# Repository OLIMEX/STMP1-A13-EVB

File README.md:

# STMP1-A13-EVB
Evaluation board for STMP15x-SOM and A13-SOM System on modules

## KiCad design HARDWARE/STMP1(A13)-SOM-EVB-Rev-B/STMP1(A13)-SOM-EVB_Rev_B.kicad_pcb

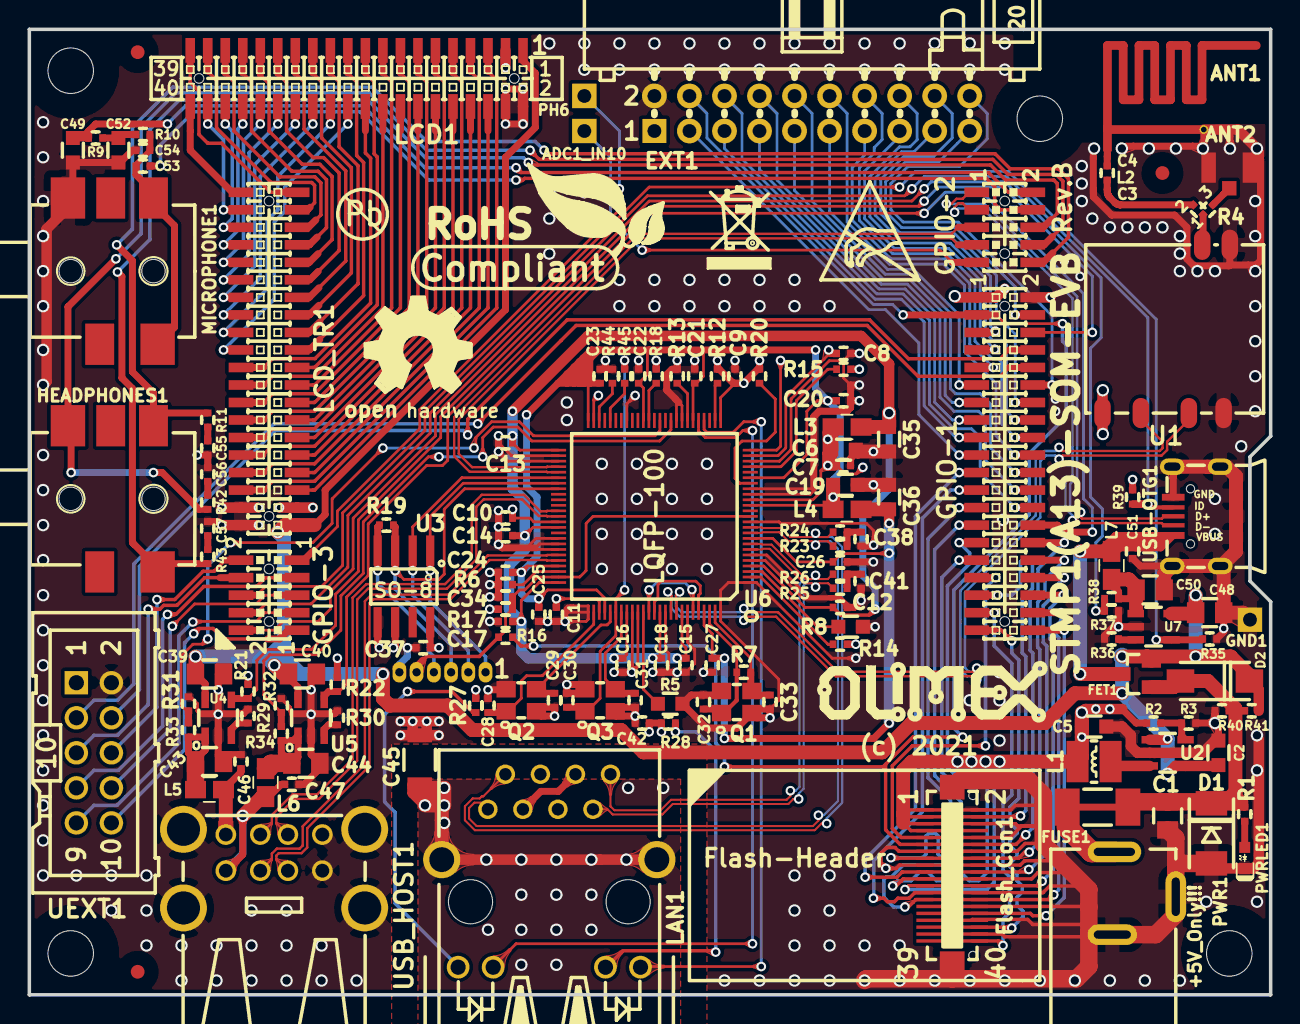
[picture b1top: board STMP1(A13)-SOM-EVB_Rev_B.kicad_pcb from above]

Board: 4 copper layers, 90.0 x 70.0 mm, 157 parts (1 on the bottom side), 164 nets.

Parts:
ADC1_IN10: TESTPAD; TEST_PAD40x70_SQUARE
ANT1: WIFI_ANT; WIFI_ANT_ESP8266_ANT(1)_GND(2)_NO_MASK
ANT2: U.FL-R-SMT-1
C1, C39, C40, C43, C44, C48, C50: 47uF/6.3V/20%/X5R/C0805; C_0805_5MIL_DWS
C2, C5, C6, C19, C35, C36, C49, C52: 10uF/6.3V/20%/X5R/C0603; C_0603_5MIL_DWS
C3, C4: NA/C0402; C_0402_5MIL_DWS
C7, C8, C9, C10, C11, C12, C13, C14, C15, C16, C17, C18, C20, C21, C22, C23, C24, C25, C26, C27, C34, C37, C38, C41, C42, C46, C47, C51, C53, C55, C56, C57: 100nF/10V/10%/X5R/C0402; C_0402_5MIL_DWS
C28, C29, C32, C33: 33pF/50V/5%/COG/C0402; C_0402_5MIL_DWS
C30, C31: NA(33pF/50V/5%/COG/C0402); C_0402_5MIL_DWS
C45: 1nF/2000V/10%/X7R/C1206; C_1206_5MIL_DWS_ISO
C54: 3.3nF/50V/10%/X5R/C0402; C_0402_5MIL_DWS
D1: SMBJ6.0A; DO214AA_1(K)-2(A)
D2: 1N5822/SMA; SMA-KA
EXT1: BH20R
FET1: WPM2015-3/TR; SOT23
FID1, FID2, FID3: Fiducial; Fiducial1x3
FUSE1: NA(5025); FUSE-5025
Flash_Con1: Flash_Con[DF12(3.0)-40DS-0.5V(86)]
GND1: TESTPAD; TEST_PAD40x70_SQUARE
GPIO-1: PA-V16X-2X20-LF; GPH127SMT-02X20(PA-V16X-2X20-LF)
GPIO-2, GPIO-3: PA-V16X-2X5-LF; GPH127SMT-02X05(PA-V16X-2X5-LF)
HEADPHONES1: SCJ325P00XG0B02G
L1: 2.2uH/1.5A/DCR=72mR/20%/3.00x3.00x1.50mm/CD32(NR3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; CD32
L2: 0R/R0402; L_0402_5MIL_DWS
L3, L4, L5, L6, L7: FB0805/600R/2A; L_0805_5MIL_DWS
LAN1: RJLD-060TC1(LPJ4013EDNL); RJLBC-060TC1
LCD1: PA-V16X-2X20-LF; GPH127SMT-02X20(PA-V16X-2X20-LF)
LCD_TR1: PA-V16X-2X20-LF; GPH127SMT-02X20(PA-V16X-2X20-LF)
Logo_OSHW: LOGO_OPENHARDWARE_8x8
Logo_Olimex: OLIMEX_LOGO_TB
MH1, MH2, MH3, MH4: NPTH; Mounting_Hole_Drill-3.3mm_Clerance-7mm
MICROPHONE1: SCJ325P00XG0B02G
PGM1: NA(WU06S); WU06S
PH6: TESTPAD; TEST_PAD40x70_SQUARE
PWR1: PWRJ-2mm(YDJ-1134)
PWRLED1: LED/Red/0603; LED_0603_KA
Q1: Q25MHZ/20pF/20ppm/4P/3.2x2.5mm; TSX-3.2x2.5mm_GND(3)
Q2: Q12MHZ/20pF/10ppm/4P/3.2x2.5mm; TSX-3.2x2.5mm_GND(3)
Q3: NA(Q12MHZ/20pF/10ppm/4P/3.2x2.5mm); TSX-3.2x2.5mm_GND(3)
R1, R9, R10, R44: 2.2k/R0402; R_0402_5MIL_DWS
R2: 4.99k/1%/R0402; R_0402_5MIL_DWS
R3: 1.1k/1%/R0402; R_0402_5MIL_DWS
R4: 0R/R0402(Default_1-2_Populated); ANT_SWITCH-R0402
R5, R8: 12.1k/1%/R0603; R_0603_5MIL_DWS
R6: 680R/1%/R0402; R_0402_5MIL_DWS
R7: 1M/R0402; R_0402_5MIL_DWS
R11, R19, R42, R43, R45: 22R/R0402; R_0402_5MIL_DWS
R12, R13, R14, R17, R21, R22, R31, R32, R35, R37, R39, R40: 10k/R0402; R_0402_5MIL_DWS
R15, R18, R33, R34, R38: 4.7k/R0402; R_0402_5MIL_DWS
R16, R41: NA/R0402; R_0402_5MIL_DWS
R20: NA(10k/R0402); R_0402_5MIL_DWS
R23, R24, R25, R26: 49.9R/1%/R0402; R_0402_5MIL_DWS
R27, R28: 330R/R0402; R_0402_5MIL_DWS
R29, R30, R36: 13k/1%/R0402; R_0402_5MIL_DWS
Sign_Antistatic: Val**; LOGO_ANTISTATIC_1
Sign_PB-Free: LOGO_PBFREE
Sign_RecycleBin: LOGO_RECYCLEBIN_1
Sign_RoHS: Val**; LOGO_ROHS_1
U1: MOD-RL-UM12BS-8188ETV
U2: SY8089AAAC(SOT23-5); SOT-23-5
U3: 93LC66C-I/SN(SO-8); SO-8
U4, U5, U7: SY6280AAC(SOT23-5); SOT-23-5
U6: AX88760LF(LQFP-100); LQFP-100_Pitch-0.4mm_Dimensions-12.00x12.00x1.60mm
UEXT1: BH10S
USB-OTG1: MICRO_USB\MISB-SWMM-5B_LF; USB-MICRO_MISB-SWMM-5B_LF
USB_HOST1: USBB1-FRWH-4A(USB-Ax2); USB_TWO_LEVEL

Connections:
(IO2): Flash_Con1.23, GPIO-1.29
(IO3): Flash_Con1.21, GPIO-1.31
+1.8VA: C26.1, C27.1, C36.1, L4.2, U6.9, U6.97
+3.3VA: C12.1, C13.1, C14.1, C15.1, C16.1, C17.1, C18.1, C35.1, L3.2, U6.4, U6.51, U6.65, U6.75, U6.83, U6.89, U6.93
+3V3: C5.1, C6.2, C7.1, C8.1, C9.1, C10.1, C11.1, C37.2, C42.1, EXT1.1, Flash_Con1.1, Flash_Con1.3, Flash_Con1.5, Flash_Con1.7, GPIO-1.1, L1.2, L3.1, LAN1.3, LAN1.6, LCD1.3, LCD_TR1.3, R2.2, R12.2, R14.2, R15.2, R17.2, R18.2, R20.2, R21.1, R22.1, R27.1, R28.1, R39.2, U1.1, U3.6, U3.8, U6.16, U6.24, U6.26, U6.64, U6.78, UEXT1.1
+5V_EXT: C2.1, C39.1, C40.1, C48.1, D2.1, FET1.2, LCD1.1, LCD_TR1.1, R41.1, U2.1, U2.4, U4.5, U5.5, U7.5
+5V_USBOTG: C51.1, FET1.3, L7.2, USB-OTG1.1
/12MCK: C30.1, Q3.1, R45.2, U6.81
/+5V_USB1: C46.2, L5.2, USB_HOST1.1.1
/+5V_USB2: C47.2, L6.2, USB_HOST1.2.1
/D1+: U6.63, USB_HOST1.1.3
/D1-: U6.62, USB_HOST1.1.2
/D2+: U6.71, USB_HOST1.2.3
/D2-: U6.70, USB_HOST1.2.2
/D3+: U1.3, U6.92
/D3-: U1.2, U6.91
/ETHER_LK: LAN1.KY1, U6.30
/ETHER_SPEED: LAN1.KG1, U6.29
/ETH_SH: C45.1, LAN1.GND1, LAN1.GND2
/I2C2_SCL: EXT1.17, GPIO-1.5
/I2C2_SDA: EXT1.15, GPIO-1.7
/I2C5_SCL: LCD1.39, LCD_TR1.39
/I2C5_SDA: LCD1.40, LCD_TR1.40
/I2C6_SCL: EXT1.5, GPIO-1.17
/I2C6_SDA: EXT1.3, GPIO-1.19
/LCD_B0: LCD1.21, LCD_TR1.21
/LCD_B1: LCD1.22, LCD_TR1.22
/LCD_B2: LCD1.23, LCD_TR1.23
/LCD_B3: LCD1.24, LCD_TR1.24
/LCD_B4: LCD1.25, LCD_TR1.25
/LCD_B5: LCD1.26, LCD_TR1.26
/LCD_B6: LCD1.27, LCD_TR1.27
/LCD_B7: LCD1.28, LCD_TR1.28
/LCD_CLK: LCD1.31, LCD_TR1.31
/LCD_DE: LCD1.32, LCD_TR1.32
/LCD_G0: LCD1.13, LCD_TR1.13
/LCD_G1: LCD1.14, LCD_TR1.14
/LCD_G2: LCD1.15, LCD_TR1.15
/LCD_G3: LCD1.16, LCD_TR1.16
/LCD_G4: LCD1.17, LCD_TR1.17
/LCD_G5: LCD1.18, LCD_TR1.18
/LCD_G6: LCD1.19, LCD_TR1.19
/LCD_G7: LCD1.20, LCD_TR1.20
/LCD_HSYNC: LCD1.29, LCD_TR1.29
/LCD_INT: LCD1.37, LCD_TR1.37
/LCD_LR: LCD1.33, LCD_TR1.33
/LCD_PWM: LCD1.36, LCD_TR1.36
/LCD_PWRE: LCD1.35, LCD_TR1.35
/LCD_R0: LCD1.5, LCD_TR1.5
/LCD_R1: LCD1.6, LCD_TR1.6
/LCD_R2: LCD1.7, LCD_TR1.7
/LCD_R3: LCD1.8, LCD_TR1.8
/LCD_R4: LCD1.9, LCD_TR1.9
/LCD_R5: LCD1.10, LCD_TR1.10
/LCD_R6: LCD1.11, LCD_TR1.11
/LCD_R7: LCD1.12, LCD_TR1.12
/LCD_RST: LCD1.38, LCD_TR1.38
/LCD_UD: LCD1.34, LCD_TR1.34
/LCD_VSYNC: LCD1.30, LCD_TR1.30
/NRST: EXT1.4, Flash_Con1.11, GPIO-1.3, R16.2
/OVCUR1#: R31.2, R33.1, U6.37
/OVCUR2#: R32.2, R34.1, U6.35
/PA1: EXT1.19, GPIO-1.4
/PG8: EXT1.7, GPIO-1.15
/RST_PGM: C34.2, PGM1.5, R16.1, R17.1, U6.13, U6.74
/RXIN: LAN1.8, R26.2, U6.8
/RXIP: LAN1.7, R25.2, U6.7
/SDMMC3_CK: EXT1.16, GPIO-1.16
/SDMMC3_CMD: EXT1.14, GPIO-1.18
/SDMMC3_D0: EXT1.6, GPIO-1.26
/SDMMC3_D1: EXT1.8, GPIO-1.24
/SDMMC3_D2: EXT1.10, GPIO-1.22
/SDMMC3_D3: EXT1.12, GPIO-1.20
/TXON: LAN1.2, R24.2, U6.11
/TXOP: LAN1.1, R23.2, U6.10
/USART3_RX: EXT1.9, GPIO-1.13
/USART3_TX: EXT1.11, GPIO-1.11
/USB1-DRV: GPIO-1.6, R21.2, U4.4
/USB2-DRV: GPIO-1.28, R22.2, U5.4
/USB-OTG-DRV: GPIO-3.6, R35.2, U7.4
/USB_OTG_HS_ID: GPIO-3.4, R39.1, USB-OTG1.4
/USB_OTG_HS_VBUS: GPIO-3.2, R37.2, R38.1
/V18F: C19.2, C20.1, C21.1, C22.1, C23.1, C24.1, C25.1, L4.1, U6.15, U6.20, U6.31, U6.40, U6.50, U6.72, U6.79
/eMMC-CLK: Flash_Con1.4, GPIO-1.35
/eMMC-CMD: Flash_Con1.9, GPIO-1.33
/eMMC-D0: Flash_Con1.40, GPIO-1.37
/eMMC-D1: Flash_Con1.36, GPIO-1.39
/eMMC-D2: Flash_Con1.32, GPIO-1.40
/eMMC-D3: Flash_Con1.28, GPIO-1.38
/eMMC-D4: Flash_Con1.24, GPIO-1.36
/eMMC-D5: Flash_Con1.20, GPIO-1.34
/eMMC-D6: Flash_Con1.16, GPIO-1.32
/eMMC-D7: Flash_Con1.12, GPIO-1.30
GND: ANT1.1, ANT1.2, ANT2.2, C1.1, C2.2, C3.2, C4.1, C4.2, C5.2, C6.1, C7.2, C8.2, C9.2, C10.2, C11.2, C12.2, C13.2, C14.2, C15.2, C16.2, C17.2, C18.2, C19.1, C20.2, C21.2, C22.2, C23.2, C24.2, C25.2, C26.2, C27.2, C28.2, C29.2, C30.2, C31.2, C32.2, C33.2, C34.1, C35.2, C36.2, C37.1, C38.1, C39.2, C40.2, C41.1, C42.2, C43.1, C44.1, C45.2, C46.1, C47.1, C48.2, C49.2, C50.1, C51.2, C52.2, C54.2, C55.2, C56.2, C57.2, D1.2, EXT1.2, Flash_Con1.0, Flash_Con1.2, Flash_Con1.6, Flash_Con1.10, Flash_Con1.13, Flash_Con1.14, Flash_Con1.17, Flash_Con1.18, Flash_Con1.22, Flash_Con1.26, Flash_Con1.30, Flash_Con1.34, Flash_Con1.38, GND1.1, GPIO-1.2, L2.2, LCD1.2, LCD1.4, LCD_TR1.2, LCD_TR1.4, MICROPHONE1.2, PGM1.6, PWR1.-, PWRLED1.1, Q1.3, Q2.3, Q3.3, R3.2, R5.1, R6.1, R8.2, R13.2, R29.1, R30.1, R31.1, R32.1, R35.1, R36.1, R37.1, R40.1, R44.2, U1.4, U1.5, U2.2, U3.5, U4.2, U5.2, U6.1, U6.5, U6.6, U6.12, U6.17, U6.18, U6.23, U6.33, U6.34, U6.43, U6.49, U6.52, U6.53, U6.67, U6.68, U6.69, U6.76, U6.84, U6.85, U6.90, U6.94, U6.100, U7.2, UEXT1.2, USB-OTG1.0, USB-OTG1.5, USB_HOST1.0, USB_HOST1.1.4, USB_HOST1.2.4
HPCOM: GPIO-2.8, HEADPHONES1.2, R42.2
HPOUT1L: GPIO-2.6, HEADPHONES1.1, R43.2
HPOUT1R: GPIO-2.10, HEADPHONES1.3, R11.2
I2C3_SCL: GPIO-3.8, UEXT1.5
I2C3_SDA: GPIO-3.10, UEXT1.6
LPTIM5_OUT: EXT1.13, GPIO-1.9
MICIN1: C53.2, GPIO-2.4
unnamed: ADC1_IN10.1, GPIO-2.9
unnamed: ANT2.1, R4.3
unnamed: C1.2, D1.1, D2.2, FET1.1, FUSE1.1, FUSE1.2, PWR1.+, R1.1, R40.2, R41.2
unnamed: C3.1, L2.1, R4.2
unnamed: C28.1, Q2.1, U6.77
unnamed: C29.1, Q2.2, U6.80
unnamed: C31.1, Q3.2, U6.82
unnamed: C32.1, Q1.1, R7.1, U6.98
unnamed: C33.1, Q1.2, R7.2, U6.99
unnamed: C38.2, R23.1, R24.1
unnamed: C41.2, R25.1, R26.1
unnamed: C43.2, L5.1, R33.2, U4.1
unnamed: C44.2, L6.1, R34.2, U5.1
unnamed: C50.2, L7.1, R38.2, U7.1
unnamed: C52.1, R9.1, R10.2
unnamed: C53.1, C54.1, MICROPHONE1.1, MICROPHONE1.3, R10.1
unnamed: C55.1, R11.1
unnamed: C56.1, R42.1
unnamed: C57.1, R43.1
unnamed: GPIO-3.9, PH6.1
unnamed: L1.1, U2.3
unnamed: LAN1.AG1, R28.2
unnamed: LAN1.AY1, R27.2
unnamed: PGM1.1, U3.1, U6.57
unnamed: PGM1.2, U3.2, U6.56
unnamed: PGM1.3, R19.1, U3.3, U6.58
unnamed: PGM1.4, R19.2, U3.4
unnamed: PWRLED1.2, R1.2
unnamed: R2.1, R3.1, U2.5
unnamed: R4.1, U1.6
unnamed: R5.2, U6.86
unnamed: R6.2, U6.73
unnamed: R8.1, U6.3
unnamed: R12.1, U6.27
unnamed: R13.1, U6.32
unnamed: R14.1, U6.2
unnamed: R15.1, U6.22
unnamed: R18.1, U6.39
unnamed: R20.1, U6.19
unnamed: R29.2, U4.3
unnamed: R30.2, U5.3
unnamed: R36.2, U7.3
unnamed: R44.1, U6.48
unnamed: R45.1, U6.46
unnamed: U6.87, U6.95
unnamed: U6.88, U6.96
SPI0_MISO(IO1): Flash_Con1.25, GPIO-1.23
SPI0_MOSI(IO0): Flash_Con1.19, GPIO-1.21
SPI0_NSS(CSn): Flash_Con1.27, GPIO-1.27
SPI0_SCK(CLK): Flash_Con1.15, GPIO-1.25
SPI4_MISO: GPIO-3.7, UEXT1.7
SPI4_MOSI: GPIO-3.5, UEXT1.8
SPI4_NSS: GPIO-3.1, UEXT1.10
SPI4_SCK: GPIO-3.3, UEXT1.9
UART7_RX: GPIO-1.8, UEXT1.4
UART7_TX: GPIO-1.10, UEXT1.3
USART1_RX: EXT1.20, GPIO-1.12
USART1_TX: EXT1.18, GPIO-1.14
USB1_D+: GPIO-2.5, U6.55
USB1_D-: GPIO-2.7, U6.54
USB_OTG_HS_D+: GPIO-2.1, USB-OTG1.3
USB_OTG_HS_D-: GPIO-2.3, USB-OTG1.2
VMIC: C49.1, GPIO-2.2, R9.2

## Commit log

2021-05-21 initial upload

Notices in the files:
HARDWARE/STMP1(A13)-SOM-EVB-Rev-B/STMP1(A13)-SOM-EVB_Rev_B.kicad_pcb:
(c) 2021
